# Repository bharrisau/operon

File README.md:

operon
=======

Flexible ARM based temperature controller.

## License

Copyright 2013 Ben Harris
Copyright and related rights are licensed under the Solderpad Hardware License, Version 0.51 (the “License”); you may not use this file except in compliance with the License. You may obtain a copy of the License at http://solderpad.org/licenses/SHL-0.51. Unless required by applicable law or agreed to in writing, software, hardware and materials distributed under this License is distributed on an “AS IS” BASIS, WITHOUT WARRANTIES OR CONDITIONS OF ANY KIND, either express or implied. See the License for the specific language governing permissions and limitations under the License.

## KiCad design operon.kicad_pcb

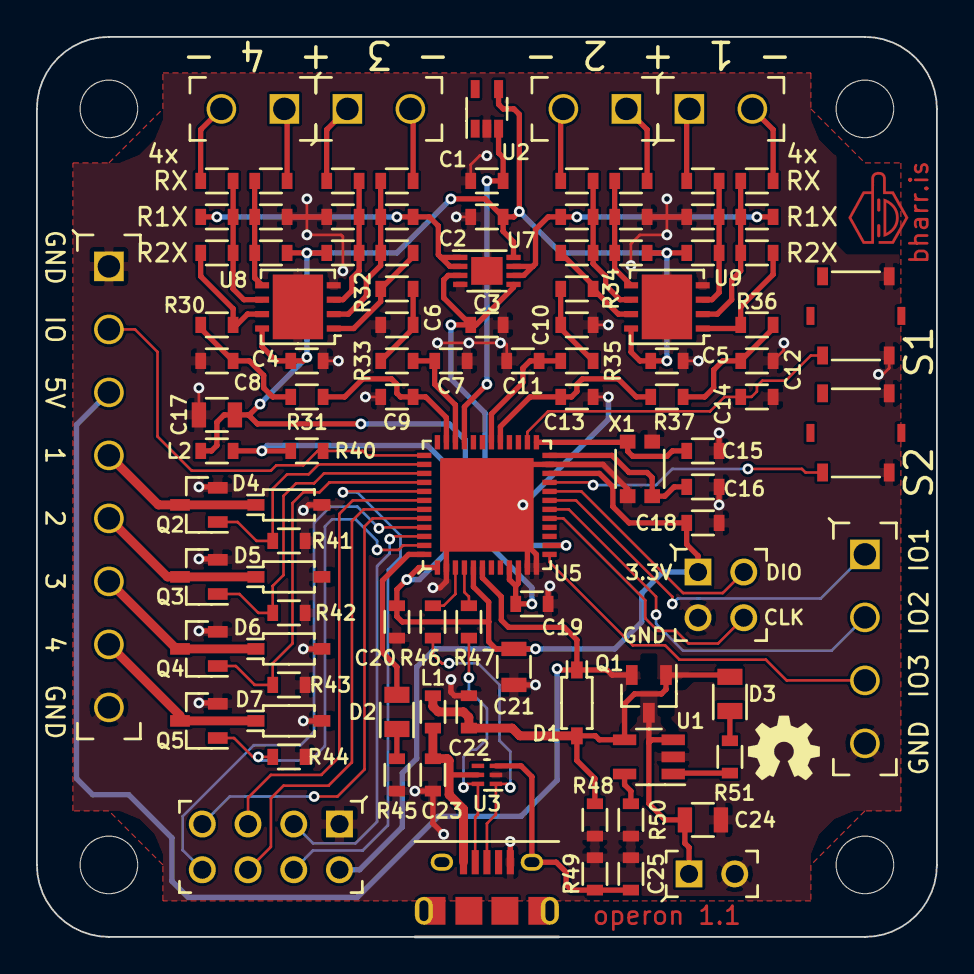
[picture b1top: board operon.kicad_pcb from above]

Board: 2 copper layers, 50.0 x 50.0 mm, 107 parts (0 on the bottom side), 73 nets.

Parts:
BT1: BATTERY; HEADER254P1X2
C1, C3, C6, C7, C8, C9, C10, C11, C12, C13, C14: 100n; CAPC1608N
C2, C4, C5, C18, C19, C20, C22, C23: 1u; CAPC1608N
C15, C16: 6p; CAPC1608N
C17, C21, C24: 22u; CAPC2012N
C25: 10n; CAPC1608N
D1: 1N5819HW; SOD3717X135N
D2, D3: LED; LEDC2012N
D4, D5, D6, D7: ZENER; SOD3717X135N
HOLE_M3, HOLE_M3#2, HOLE_M3#3, HOLE_M3#4: Val**; HOLE_M3
L1, L2: FBlow; INDC1608N
P1: USB; FCI_10118194
P3: MOD_SWD
P4: HEADER1; HEADER350P1X8
P5: HEADER2; HEADER350P1x4
P6: TC1; HEADER350P1X2
P7: TC2; HEADER350P1X2
P8: TC3; HEADER350P1X2
P9: TC4; HEADER350P1X2
Q1: AO3401A; SOT190P230X100-3N
Q2, Q3, Q4, Q5: ZXMN3A01F; SOT190P230X100-3N
R1, R2, R3, R4, R5, R6, R7, R8: 100 0.1%; RESC1608N
R11, R12, R13, R14, R15, R16, R17, R18: 5.6k 0.1%; RESC1608N
R21, R22, R23, R24, R25, R26, R27, R28: 100k 0.1%; RESC1608N
R30, R31, R32, R33, R34, R35, R36, R37: 510; RESC1608N
R40, R45, R51: 4.7k; RESC1608N
R41, R42, R43, R44, R48: 100k; RESC1608N
R46, R47: 33; RESC1608N
R49: 1M; RESC1608N
R50: 10k; RESC1608N
S1, S2: SW_PUSH; SW_EVQ
U1: MCP73831T-2ACI_OT
U2: MCP9700AT-E_LT
U3: IP4221CZ6-S
U5: MKL25Z64VFT4
U6: MOD_NRF24L01; MOD_nRF24L01
U7: MCP6002-I_MC
U8, U9: MCP6V02-E_MD
X1: HC-46X 16M; OSC-3225

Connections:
+3.3V: C18.1, C20.1, C21.1, L2.1, P3.1, R40.2, U5.1, U5.5, U5.22, U6.2
+3.3VADC: C2.1, C4.1, C5.1, C17.1, C19.1, L2.2, R22.2, R23.2, R26.2, R27.2, U2.4, U5.9, U5.10, U7.8, U8.8, U9.8
+5V: D1.2, P4.3, Q1.S, U5.6
/AFE/DAC: C3.1, U5.14, U7.3, U7.5
/AFE/SHIFT1: R11.1, R14.1, U7.1, U7.2
/AFE/SHIFT2: R15.1, R18.1, U7.6, U7.7
/AFE/TC1: C7.1, R33.2, U5.34
/AFE/TC1+: R3.2, R13.2, R23.1, U8.3
/AFE/TC1-: R4.2, R14.2, R24.1, U8.2
/AFE/TC1_OUT: R24.2, R32.1, U8.1
/AFE/TC2: C9.1, R31.2, U5.35
/AFE/TC2+: R2.2, R12.2, R22.1, U8.5
/AFE/TC2-: R1.2, R11.2, R21.1, U8.6
/AFE/TC2_OUT: R21.2, R30.1, U8.7
/AFE/TC3: C13.1, R37.2, U5.29
/AFE/TC3+: R7.2, R17.2, R27.1, U9.3
/AFE/TC3-: R8.2, R18.2, R28.1, U9.2
/AFE/TC3_OUT: R28.2, R36.1, U9.1
/AFE/TC4: C11.1, R35.2, U5.30
/AFE/TC4+: R6.2, R16.2, R26.1, U9.5
/AFE/TC4-: R5.2, R15.2, R25.1, U9.6
/AFE/TC4_OUT: R25.2, R34.1, U9.7
/BUTTON: S2.1, U5.21
/CE: U5.46, U6.3
/CHG: R51.1, U1.1
/CLKIN: C16.2, U5.24, X1.1
/CLKOUT: C15.2, U5.25, X1.2
/COLD: C1.1, U2.3, U5.33
/CS: U5.41, U6.4
/D+: P1.3, R46.2, U3.1
/D-: P1.2, R47.2, U3.6
/DAL: P4.2, R40.1, U5.37
/FET1: D4.2, P4.4, Q2.D
/FET2: D5.2, P4.5, Q3.D
/FET3: D6.2, P4.6, Q4.D
/FET4: D7.2, P4.7, Q5.D
/GPIO1: P5.1, U5.19
/GPIO2: P5.2, U5.18
/GPIO3: P5.3, U5.13
/IRQ: U5.45, U6.8
/LED: D2.1, U5.48
/MISO: U5.44, U6.7
/MOSI: U5.43, U6.6
/RESET: C14.1, S1.1, U5.26
/S1: Q2.G, R41.1, U5.38
/S2: Q3.G, R42.1, U5.39
/S3: Q4.G, R43.1, U5.40
/S4: Q5.G, R44.1, U5.47
/SCK: U5.42, U6.5
/SHIELD: C25.1, P1.6, R49.2, U3.3
/SWD_CLK: P3.4, U5.17
/SWD_DIO: P3.2, U5.20
/VBUS: C23.1, L1.1, P1.1, U3.5
/VBUS2: C22.1, D1.1, D3.1, L1.2, Q1.G, R48.1, U1.4
GND: BT1.2, C1.2, C2.2, C3.2, C4.2, C5.2, C6.2, C7.2, C8.2, C9.2, C10.2, C11.2, C12.2, C13.2, C14.2, C15.1, C16.1, C17.2, C18.2, C19.2, C20.2, C21.2, C22.2, C23.2, C24.2, C25.2, D4.1, D5.1, D6.1, D7.1, P1.5, P3.3, P4.1, P4.8, P5.4, Q2.S, Q3.S, Q4.S, Q5.S, R12.1, R13.1, R16.1, R17.1, R41.2, R42.2, R43.2, R44.2, R45.1, R48.2, R49.1, R50.2, S1.2, S2.2, U1.2, U2.2, U3.2, U5.2, U5.11, U5.12, U5.23, U5.49, U6.1, U7.4, U7.9, U8.4, U8.9, U9.4, U9.9, X1.3
unnamed: R46.1, U5.3
unnamed: R47.1, U5.4
unnamed: D3.2, R51.2
unnamed: BT1.1, C24.1, Q1.D, U1.3
unnamed: D2.2, R45.2
unnamed: R50.1, U1.5
unnamed: C8.1, R30.2, R31.1
unnamed: C12.1, R36.2, R37.1
unnamed: C6.1, R32.2, R33.1
unnamed: C10.1, R34.2, R35.1
unnamed: P8.2, R8.1
unnamed: P8.1, R7.1
unnamed: P9.2, R5.1
unnamed: P9.1, R6.1
unnamed: P6.2, R4.1
unnamed: P6.1, R3.1
unnamed: P7.2, R1.1
unnamed: P7.1, R2.1

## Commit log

2013-08-27 initial
2013-08-27 .gitignore
2013-08-29 footprint defs to go
2013-08-29 pulldowns on mosfets
2013-08-29 wired
2013-08-30 ready to route
2013-08-30 Moved to QFN footprints. Still routing.
2013-09-05 working
2013-09-06 layout done
2013-09-06 kicad got confused
2013-09-06 rerouted
2013-09-06 schematic
2013-09-06 almost
2013-09-07 first version
2013-09-15 Create gh-pages branch via GitHub
2013-09-15 webmaster tools
2013-09-19 blank foundation
2013-09-20 first draft
2013-09-20 grammar
2013-09-20 grammar again
2013-09-20 CNAME setup
2013-09-25 created bom
2013-10-01 Corrected footprint for MCP6V02-E/MD (was 2x3, actually 4x4) Added 'edalm:' prefix to footprints Changed version number to 1.0 (not finalised)
2013-10-11 Reversed battery p-channel FET
2013-10-15 Add tracking
2013-10-30 setting up toolchain
2013-10-31 Bootstrapping firmware
2013-11-01 Basic application builds and runs
2013-11-01 Optimised Makefile
2013-11-01 Using 0x400 flash start now that config fields are included
2013-11-01 Moved to local programmer submodule
